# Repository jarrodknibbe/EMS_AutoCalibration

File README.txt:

We have been researching auto-calibration techniques for high-density Electric Muscle Stimulation.

In this repository, you will find the implementation details and source code of our initial prototype. 

To begin, please read the following paper:

Knibbe, J., Strohmeier, P., Boring, S., Hornbaek, K., Automatic Calibration of High Density Electric Muscle Stimulation, ACM IMWUT, September 2017.

To cut a long story short, EMS (Electric Muscle Stimulation) has two outstanding problems: (1) It is low resolution - we cannot target all muscles sufficiently to stimulate a full range of natural movement, and (2) calibration is hard. 

Typically, EMS uses pairs of large electrodes to target large muscle bodies. This enables us to control coarse movements, such as flexing the hand in and out. We believe that, in order to achieve higher resolution control (such as individual finger targeting), we need to use many smaller electrodes simultaneously. So instead of writing from 1 anode electrode to 1 cathode, we need to write from 8 anodes to 12 cathodes, or 14 anodes to 3 cathodes, or so on. This leads to another problem - calibration.

Even when only using pairs of large electrodes, calibration is a challenge. You have to find the optimal location for the electrodes and the optimal stimulation parameters. This involves placing, removing, re-placing electrodes and trial and error parameter exploration. This can easily take 5 minutes, and needs to be done per participant and per target movement. So, if you want to build an interactive system with only 4 movements, you are looking at 20 minutes of calibration prior to every use. 

If we now cover the arm in electrodes, as we intend to, the calibration process becomes increasingly complex - we now have to determine what combination of our electrodes to use for any movement. This explodes the possible unique combination of electrodes to 3^^n - 2^^n+1 + 2 (where n is the total number of electrodes). Clearly this is infeasible to test. 

So, we use EMG (electromyography) to read muscle activity between all electrodes and use this to inform our stimulation patterns with EMS. This means that the user manually performs a pose they would like to use, while we read EMG data, then we can use EMS to get them to re-perform that pose. 

In this repository, you will find the details of our prototype system for exploring this. The prototype includes a sports sleeve of 60 electrodes and the associated switching circuitry. We also include all of the control software.

If you use this, please cite:

Knibbe, J., Strohmeier, P., Boring, S., Hornbaek, K., Automatic Calibration of High Density Electric Muscle Stimulation, ACM IMWUT, September 2017.

Disclaimer:

Be careful. EMS can be dangerous or, at the very least, uncomfortable. You use the information here at your own risk.

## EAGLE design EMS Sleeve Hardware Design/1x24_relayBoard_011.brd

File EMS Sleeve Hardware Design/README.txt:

The hardware schematics included here are for an initial prototype to support our work. 

Each circuit board consists of:
- 3 shift registers SN74HC595N
- 24 solid state relays CPC1218Y

This enables switching control over 6 electrodes. As we have 60 electrodes in our prototype, we stacked 10 of the boards. The boards are designed to stack into a tower using alternating headers. 

Besides our custom circuit boards, we also use 1 off-the-shelf EMS unit (Med-Fit 1, though anything similar would do) and 2 EMG devices (Backyard Brains Muscle Spiker Shields). We remove the manual potentiometers from the EMS device and replace them with digital potentiometers (DS1803-050). This gives digital control over the amplitude, pulse width and frequency of the stimulation signal. 

All circuitry connects to an Arduino Mega. This cannot provide enough current to support the signal switching board, so we use a second Arduino Mega. This could also be provide by batteries, a power suplly, etc. Both of the Muscle Spiker Shields (for EMG) take their own Arduino Uno. 

There are undoubtedly optimisations and improvements that can be made. Current limitations or points for consideraion:

1. Our design did not focus on a small form factor, so ends up being quite large (as can be seen in the figures in the associated paper). 
2. We have reason to believe that our choice of relay (CPC1218Y) was also not sufficient for switching all possible signals out of our EMS device (the voltage can go above the limit of the relay). We never noticed any failure behaviour, but a CPC1215 may be more appropriate. I think, if I were to make the adjustments for a different relay, I would consider smaller surface mount relay options, to reduce the overall form factor. 
3. The EMG read process is too slow. The switching of the relays introduces noise to the EMG signal, requiring waiting between switching and reading. This means that our device can only read information for poses, not dynamic gestures. In the future, more EMG devices are needed to increase the speed of the reading cycle. 
4. The resolution of the Muscle Spiker Shields is too low. A higher-bit ADC is required to get the most out of the signal.

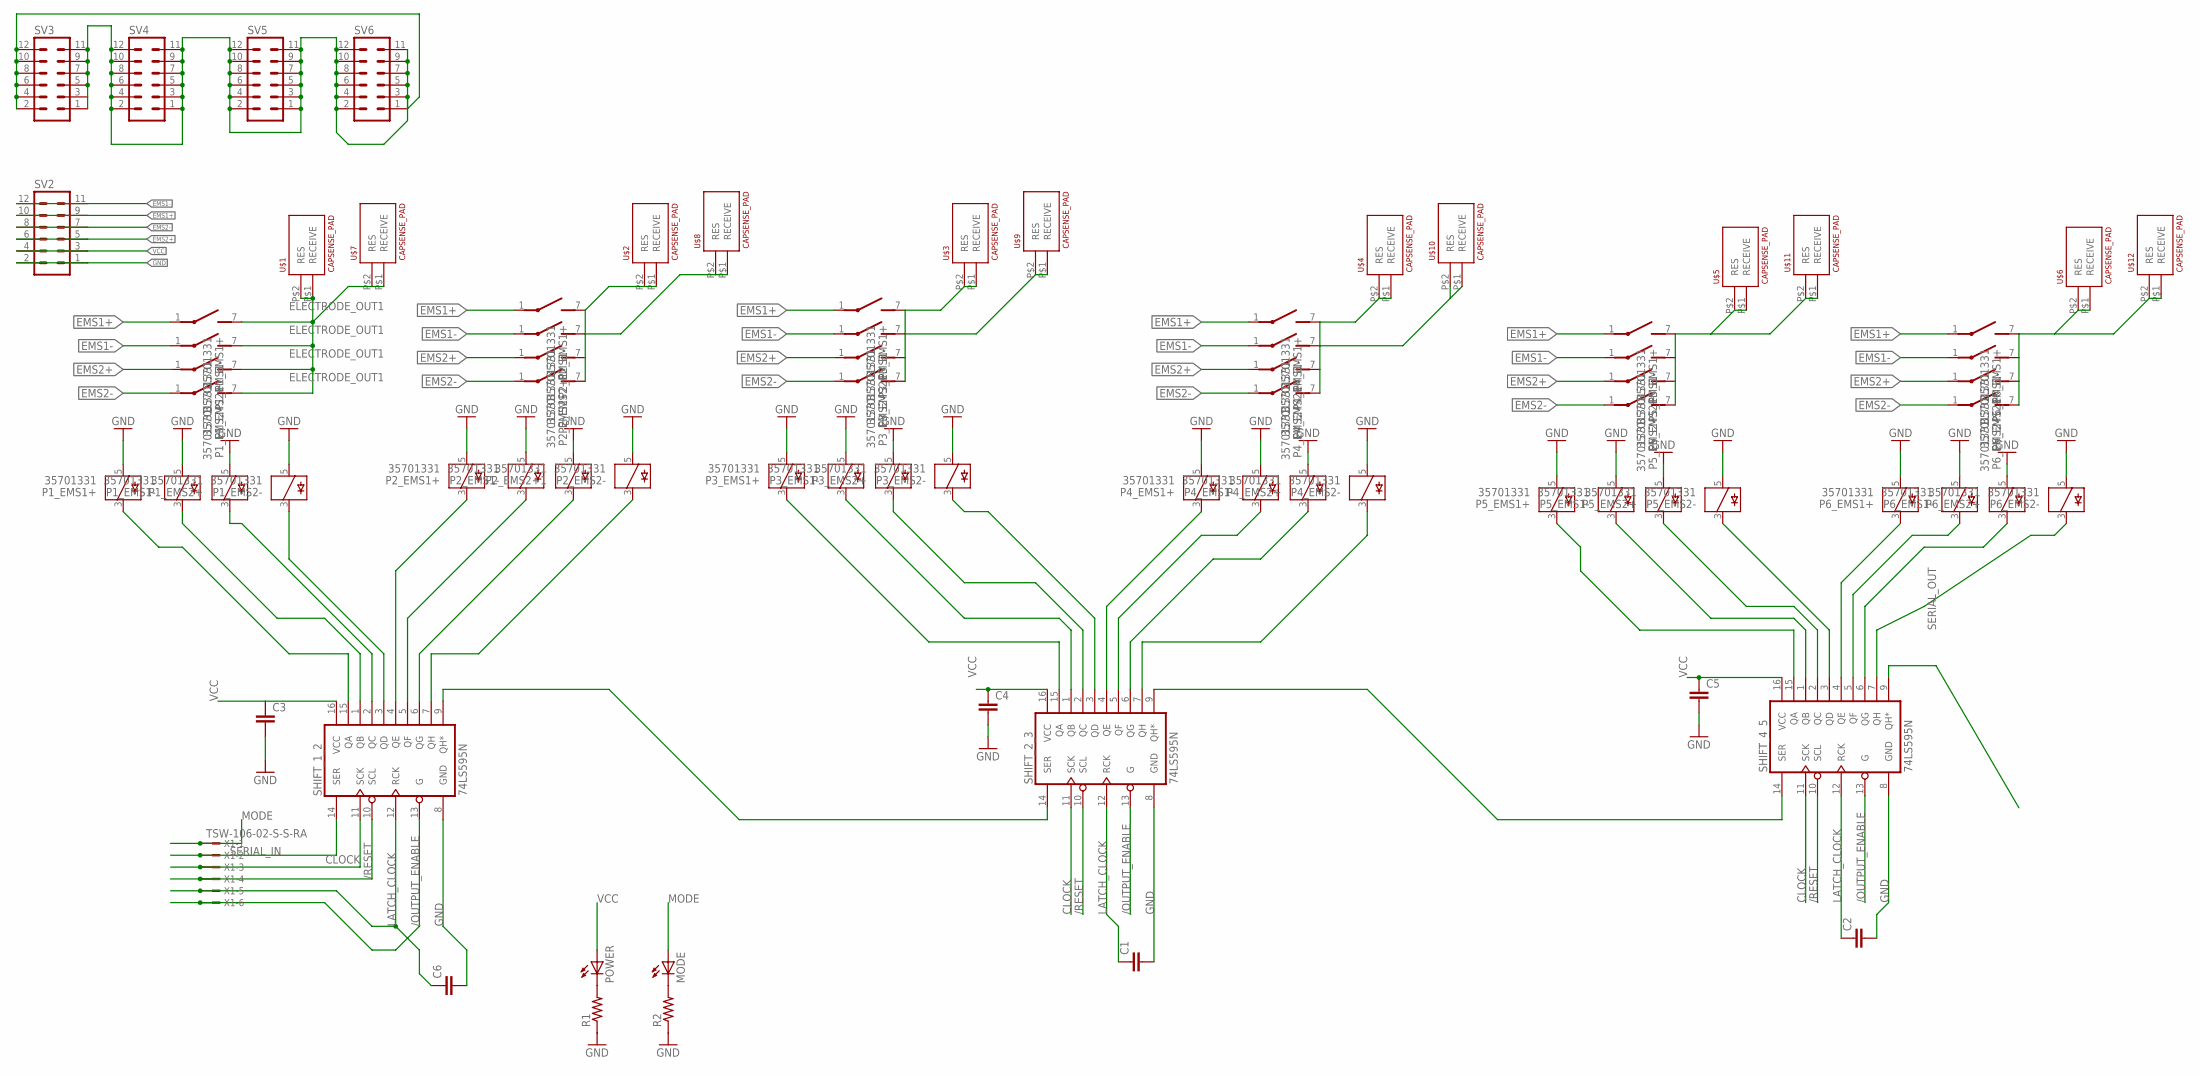
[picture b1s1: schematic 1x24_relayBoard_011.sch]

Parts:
C1, C2, C3, C4, C5, C6: C5/5; C5B5
MODE: LED_E; LED_1206
P1_EMS1+, P1_EMS1-, P1_EMS2+, P1_EMS2-, P2_EMS1+, P2_EMS1-, P2_EMS2+1, P2_EMS2-, P3_EMS1+, P3_EMS1-, P3_EMS2+, P3_EMS2-, P4_EMS1+, P4_EMS1-, P4_EMS2+, P4_EMS2-, P5_EMS1+, P5_EMS1-, P5_EMS2+, P5_EMS2-, P6_EMS1+, P6_EMS1-, P6_EMS2+, P6_EMS2-: 35701331; REED
POWER: LED_E; LED_1206
R1, R2: R-US_M1206; M1206
SHIFT_1_2, SHIFT_2_3, SHIFT_4_5: 74LS595N; DIL16
SV2, SV3, SV4, SV5, SV6: MA06-2
U$1, U$2, U$3, U$4, U$5, U$6, U$7, U$8, U$9, U$10, U$11, U$12: CAPSENSE_PAD
X1: TSW-106-02-S-S-RA

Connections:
/OUTPUT_ENABLE: SHIFT_1_2.13 (G), SHIFT_2_3.13 (G), SHIFT_4_5.13 (G), X1.6
/RESET: SHIFT_1_2.10 (SCL), SHIFT_2_3.10 (SCL), SHIFT_4_5.10 (SCL), X1.4
CLOCK: SHIFT_1_2.11 (SCK), SHIFT_2_3.11 (SCK), SHIFT_4_5.11 (SCK), X1.3
ELECTRODE_OUT1: P1_EMS1+.7 (S), P1_EMS1-.7 (S), P1_EMS2+.7 (S), P1_EMS2-.7 (S), U$1.P$1 (RECEIVE), U$1.P$2 (RES), U$7.P$1 (RECEIVE), U$7.P$2 (RES)
EMS1+: P1_EMS1+.1, P2_EMS1+.1, P3_EMS1+.1, P4_EMS1+.1, P5_EMS1+.1, P6_EMS1+.1, SV2.9, SV2.10
EMS1-: P1_EMS1-.1, P2_EMS1-.1, P3_EMS1-.1, P4_EMS1-.1, P5_EMS1-.1, P6_EMS1-.1, SV2.11, SV2.12
EMS2+: P1_EMS2+.1, P2_EMS2+1.1, P3_EMS2+.1, P4_EMS2+.1, P5_EMS2+.1, P6_EMS2+.1, SV2.5, SV2.6
EMS2-: P1_EMS2-.1, P2_EMS2-.1, P3_EMS2-.1, P4_EMS2-.1, P5_EMS2-.1, P6_EMS2-.1, SV2.7, SV2.8
GND: C1.2, C2.2, C3.2, C4.2, C5.2, C6.2, P1_EMS1+.5, P1_EMS1-.5, P1_EMS2+.5, P1_EMS2-.5, P2_EMS1+.5, P2_EMS1-.5, P2_EMS2+1.5, P2_EMS2-.5, P3_EMS1+.5, P3_EMS1-.5, P3_EMS2+.5, P3_EMS2-.5, P4_EMS1+.5, P4_EMS1-.5, P4_EMS2+.5, P4_EMS2-.5, P5_EMS1+.5, P5_EMS1-.5, P5_EMS2+.5, P5_EMS2-.5, P6_EMS1+.5, P6_EMS1-.5, P6_EMS2+.5, P6_EMS2-.5, R1.1, R2.1, SHIFT_1_2.8 (GND), SHIFT_2_3.8 (GND), SHIFT_4_5.8 (GND), SV2.1, SV2.2, SV3.1, SV3.2, SV3.3, SV3.4, SV3.5, SV3.6, SV3.7, SV3.8, SV3.9, SV3.10, SV3.11, SV3.12, SV4.1, SV4.2, SV4.3, SV4.4, SV4.5, SV4.6, SV4.7, SV4.8, SV4.9, SV4.10, SV4.11, SV4.12, SV5.1, SV5.2, SV5.3, SV5.4, SV5.5, SV5.6, SV5.7, SV5.8, SV5.9, SV5.10, SV5.11, SV5.12, SV6.1, SV6.2, SV6.3, SV6.4, SV6.5, SV6.6, SV6.7, SV6.8, SV6.9, SV6.10, SV6.11, SV6.12
LATCH_CLOCK: C1.1, C2.1, C6.1, SHIFT_1_2.12 (RCK), SHIFT_2_3.12 (RCK), SHIFT_4_5.12 (RCK), X1.5
MODE: MODE.A, X1.1
unnamed: P3_EMS1+.3, SHIFT_2_3.15 (QA)
unnamed: P1_EMS1+.3, SHIFT_1_2.15 (QA)
unnamed: P1_EMS1-.3, SHIFT_1_2.1 (QB)
unnamed: P1_EMS2+.3, SHIFT_1_2.2 (QC)
unnamed: P1_EMS2-.3, SHIFT_1_2.3 (QD)
unnamed: P2_EMS1+.3, SHIFT_1_2.4 (QE)
unnamed: P2_EMS1-.3, SHIFT_1_2.5 (QF)
unnamed: P2_EMS2+1.3, SHIFT_1_2.6 (QG)
unnamed: P2_EMS2-.3, SHIFT_1_2.7 (QH)
unnamed: P3_EMS1-.3, SHIFT_2_3.1 (QB)
unnamed: P3_EMS2+.3, SHIFT_2_3.2 (QC)
unnamed: P3_EMS2-.3, SHIFT_2_3.3 (QD)
unnamed: P4_EMS1+.3, SHIFT_2_3.4 (QE)
unnamed: P4_EMS1-.3, SHIFT_2_3.5 (QF)
unnamed: P4_EMS2+.3, SHIFT_2_3.6 (QG)
unnamed: P4_EMS2-.3, SHIFT_2_3.7 (QH)
unnamed: P5_EMS1+.3, SHIFT_4_5.15 (QA)
unnamed: P5_EMS1-.3, SHIFT_4_5.1 (QB)
unnamed: P5_EMS2+.3, SHIFT_4_5.2 (QC)
unnamed: P5_EMS2-.3, SHIFT_4_5.3 (QD)
unnamed: P6_EMS1+.3, SHIFT_4_5.4 (QE)
unnamed: P6_EMS1-.3, SHIFT_4_5.5 (QF)
unnamed: P6_EMS2+.3, SHIFT_4_5.6 (QG)
unnamed: P6_EMS2-.3, SHIFT_4_5.7 (QH)
unnamed: P2_EMS1+.7 (S), P2_EMS1-.7 (S), P2_EMS2+1.7 (S), P2_EMS2-.7 (S), U$2.P$1 (RECEIVE), U$2.P$2 (RES), U$8.P$1 (RECEIVE), U$8.P$2 (RES)
unnamed: P3_EMS1+.7 (S), P3_EMS1-.7 (S), P3_EMS2+.7 (S), P3_EMS2-.7 (S), U$3.P$1 (RECEIVE), U$3.P$2 (RES), U$9.P$1 (RECEIVE), U$9.P$2 (RES)
unnamed: P4_EMS1+.7 (S), P4_EMS1-.7 (S), P4_EMS2+.7 (S), P4_EMS2-.7 (S), U$4.P$1 (RECEIVE), U$4.P$2 (RES), U$10.P$1 (RECEIVE), U$10.P$2 (RES)
unnamed: P5_EMS1+.7 (S), P5_EMS1-.7 (S), P5_EMS2+.7 (S), P5_EMS2-.7 (S), U$5.P$1 (RECEIVE), U$5.P$2 (RES), U$11.P$1 (RECEIVE), U$11.P$2 (RES)
unnamed: P6_EMS1+.7 (S), P6_EMS1-.7 (S), P6_EMS2+.7 (S), P6_EMS2-.7 (S), U$6.P$1 (RECEIVE), U$6.P$2 (RES), U$12.P$1 (RECEIVE), U$12.P$2 (RES)
unnamed: SHIFT_1_2.9 (QH*), SHIFT_2_3.14 (SER)
unnamed: SHIFT_2_3.9 (QH*), SHIFT_4_5.14 (SER)
unnamed: POWER.C, R1.2
unnamed: MODE.C, R2.2
SERIAL_IN: SHIFT_1_2.14 (SER), X1.2
SERIAL_OUT: SHIFT_4_5.9 (QH*)
VCC: C3.1, C4.1, C5.1, POWER.A, SHIFT_1_2.16 (VCC), SHIFT_2_3.16 (VCC), SHIFT_4_5.16 (VCC), SV2.3, SV2.4

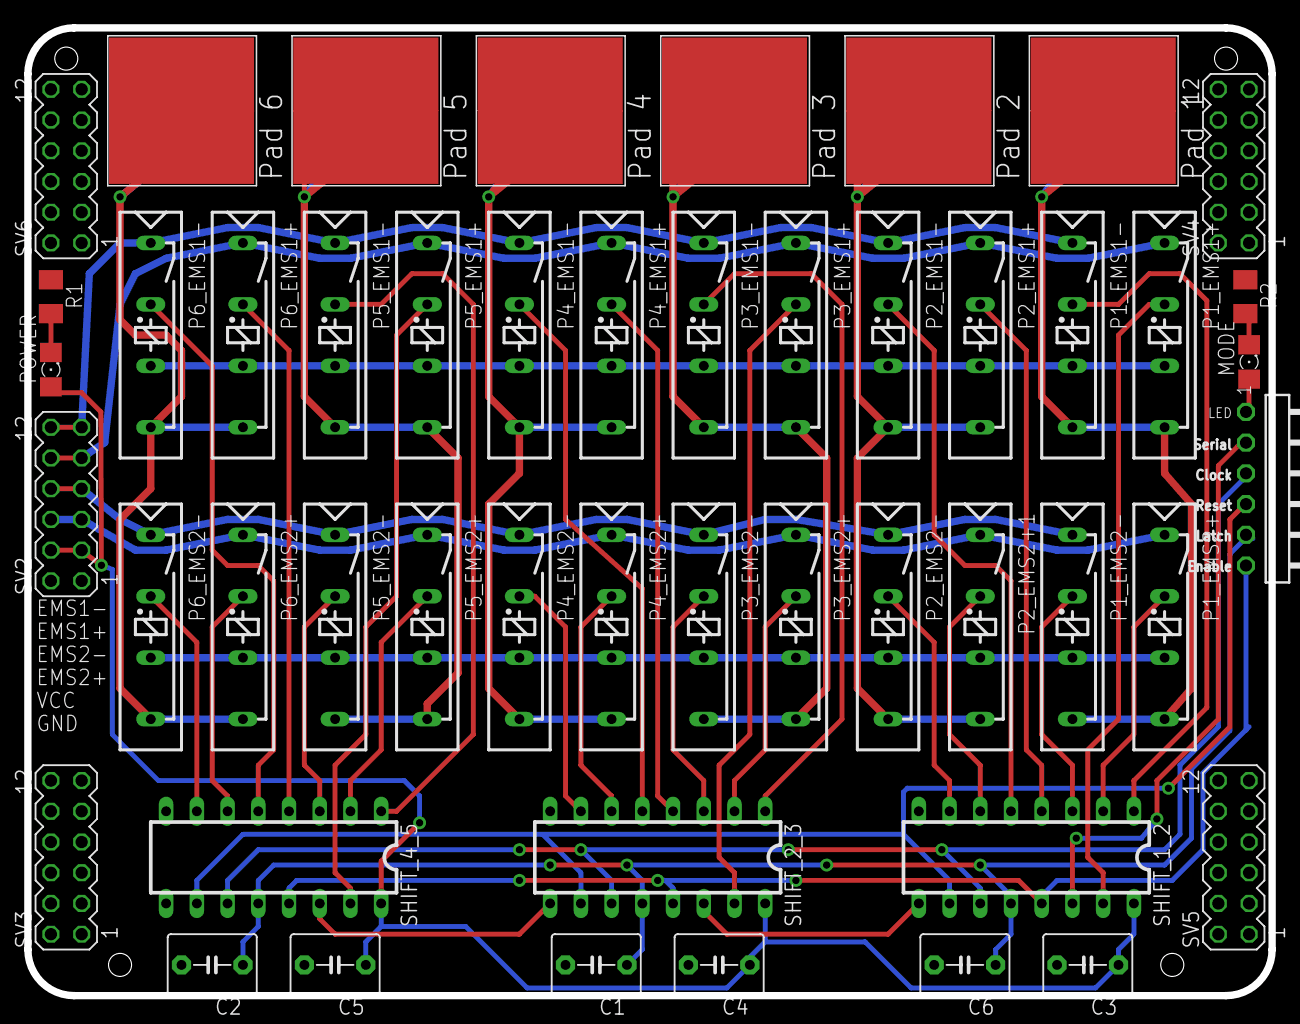
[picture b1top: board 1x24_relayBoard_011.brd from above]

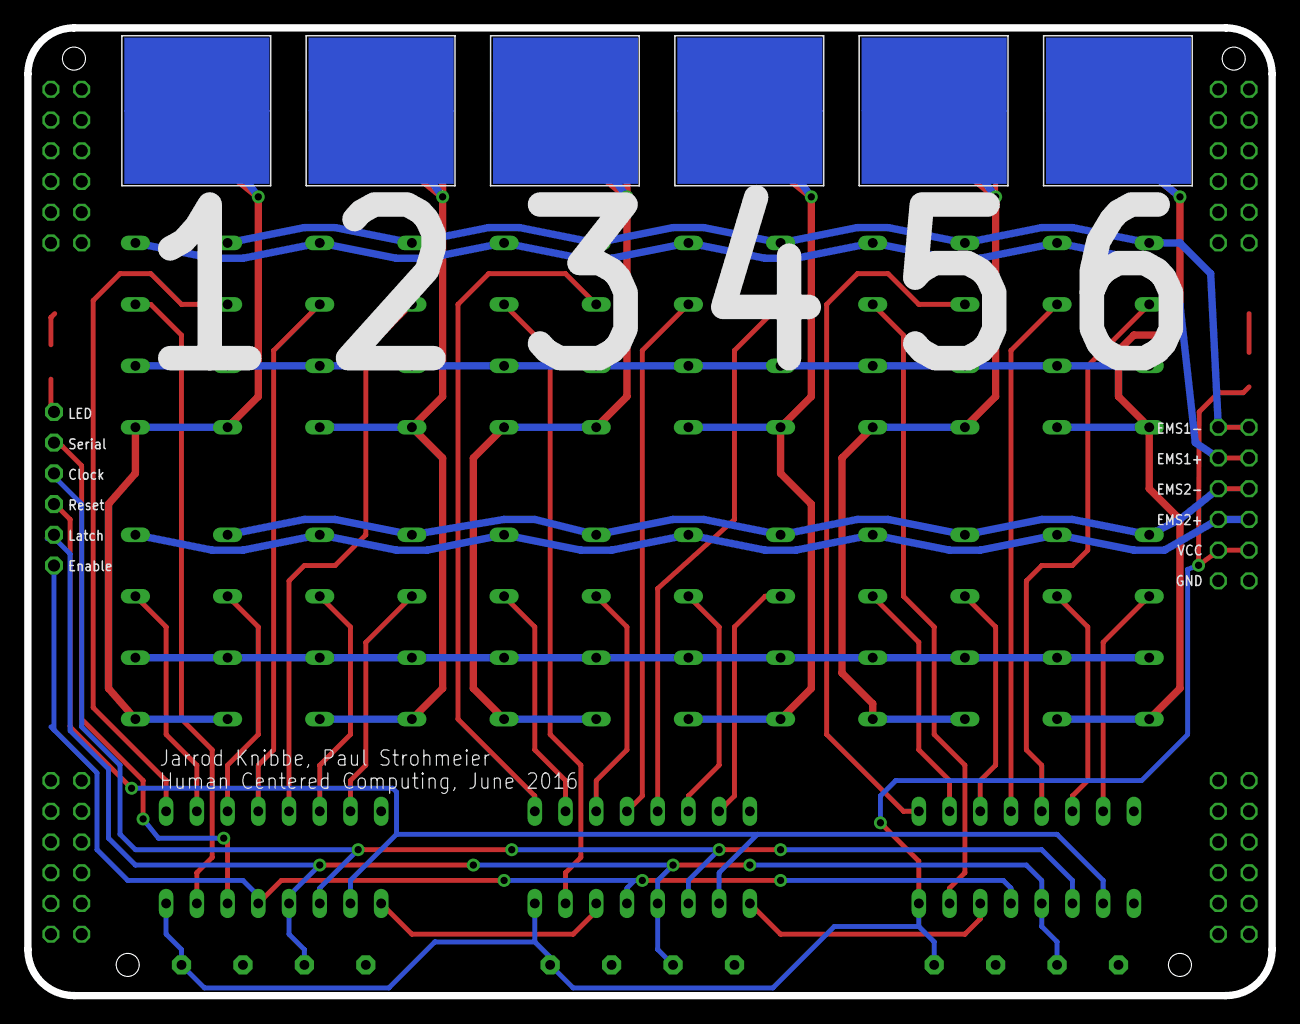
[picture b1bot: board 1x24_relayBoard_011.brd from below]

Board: 2 copper layers, 102.9 x 80.0 mm, 55 parts (6 on the bottom side), 46 nets.

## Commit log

2017-07-12 EMS_AutoCalibration Repository Creation
    Created initial README, detailing that content will follow at
    publication time.
2017-07-12 Updated reference
    Updated reference to add 'to appear'
2017-09-01 Upload of All Files
    Initial upload of everything
2017-09-01 Updated Primary Readme
    Removed placeholder text from primary readme.

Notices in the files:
parts and their libraries:
SparkFun-Electromechanical: Licensing: Creative Commons ShareAlike 4.0 International - https://creativecommons.org/licenses/by-sa/4.0
